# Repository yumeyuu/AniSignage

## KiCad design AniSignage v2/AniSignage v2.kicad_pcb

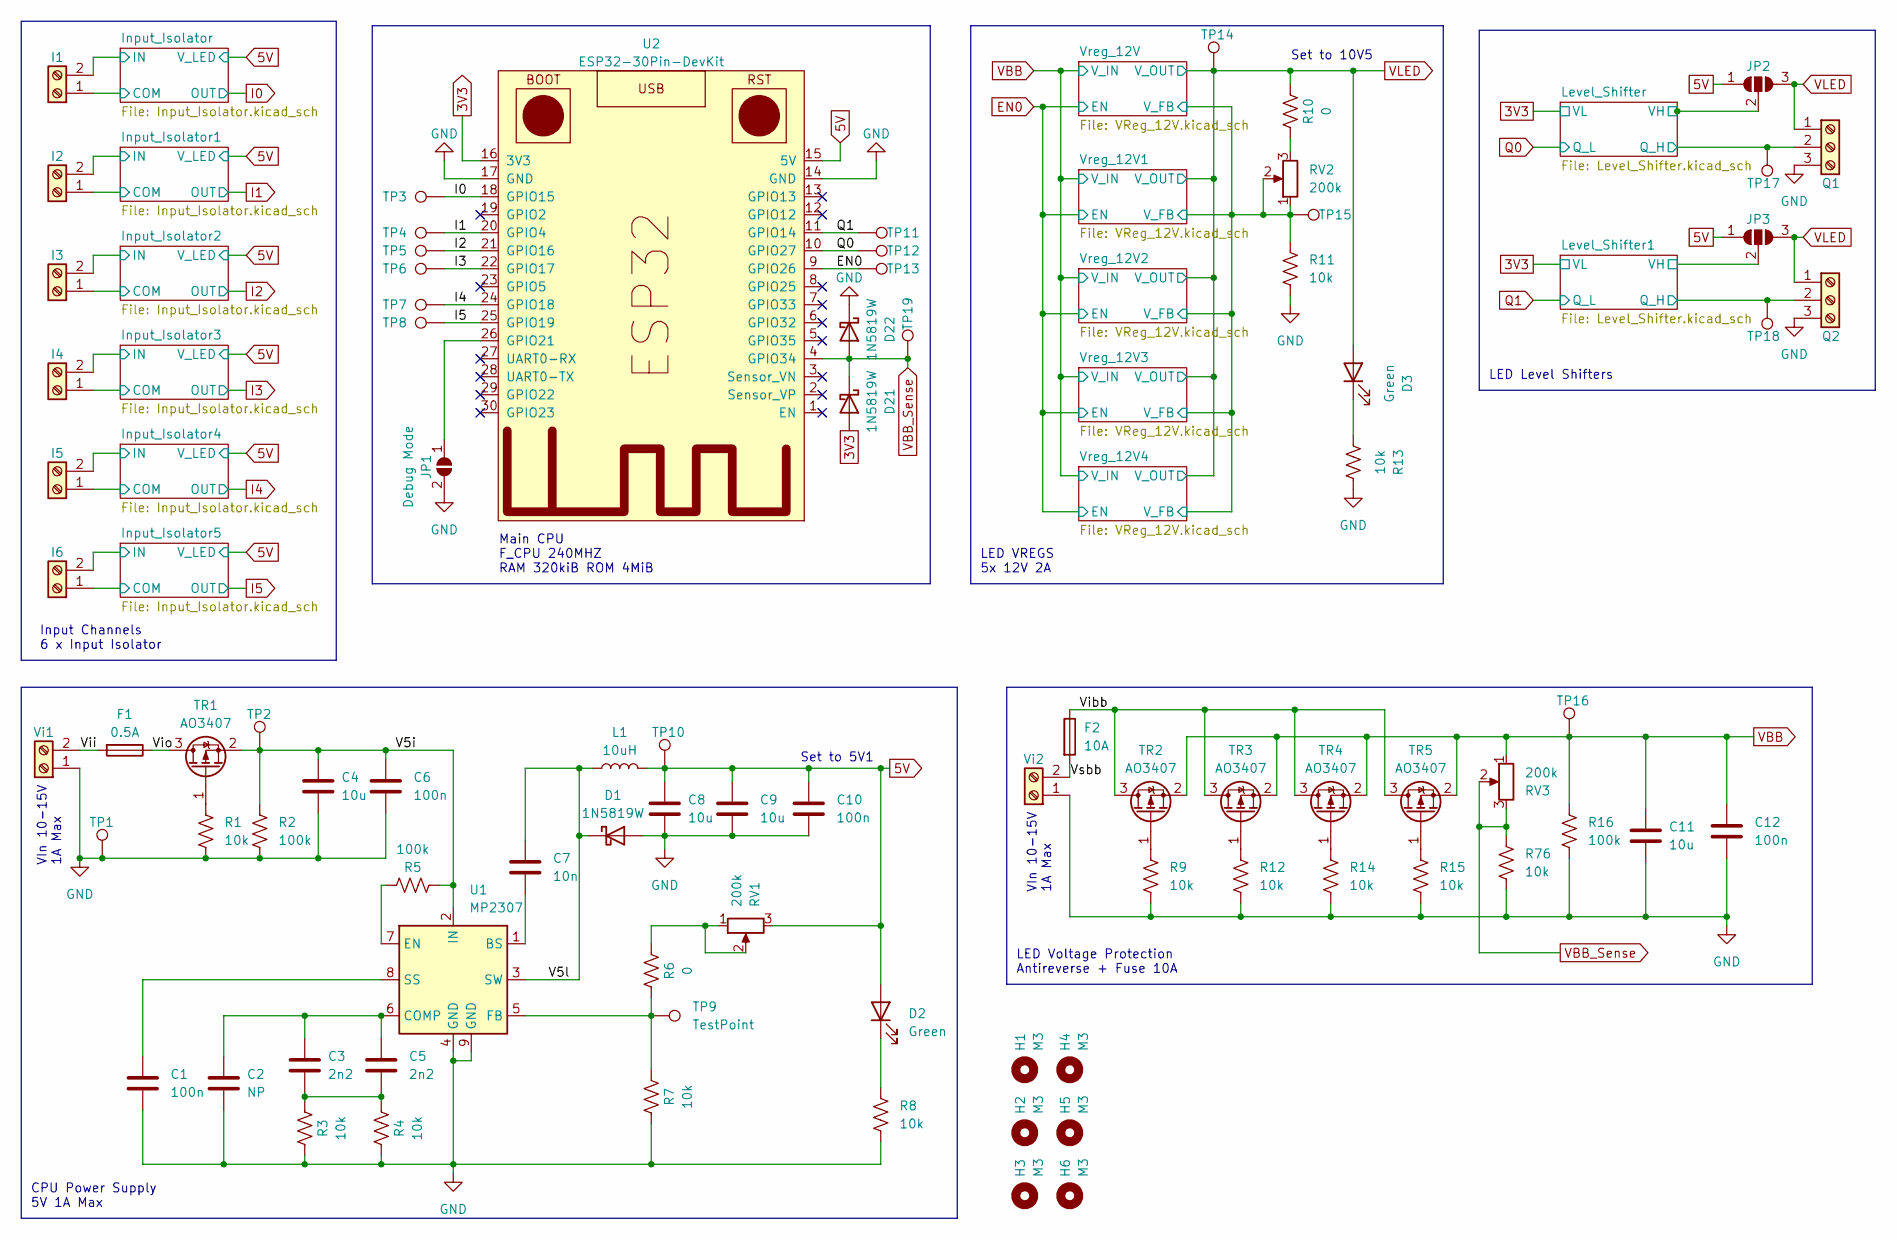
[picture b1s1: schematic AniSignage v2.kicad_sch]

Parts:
C1, C6, C10, C12: 100n; C_0603_1608Metric
C2: NP; C_0603_1608Metric
C3, C5: 2n2; C_0603_1608Metric
C4, C8, C9, C11: 10u; C_1206_3216Metric
C7: 10n; C_0603_1608Metric
D1, D21, D22: 1N5819W; D_SOD-123F
D2, D3: Green; LED_0805_2012Metric
F1: 0.5A; Fuse_1812_4532Metric
F2: 10A; Fuse_Bourns_MF-RG1100
H1, H2, H3, H4, H5, H6: M3; MountingHole_3.2mm_M3
I1, I2, I3, I4, I5, I6: Screw_Terminal_01x02; TerminalBlock_4Ucon_1x02_P3.50mm_Horizontal
JP1: Debug Mode; SolderJumper-2_P1.3mm_Open_TrianglePad1.0x1.5mm
JP2, JP3: SolderJumper_3_Open; SolderJumper-3_P2.0mm_Open_TrianglePad1.0x1.5mm
L1: 10uH; L_Neosid_SM-NE127_HandSoldering
Q1, Q2: Screw_Terminal_01x03; TerminalBlock_4Ucon_1x03_P3.50mm_Horizontal
R1, R3, R4, R7, R8, R9, R11, R12, R13, R14, R15, R76: 10k; R_0603_1608Metric
R2, R5, R16: 100k; R_0603_1608Metric
R6, R10: 0; R_0603_1608Metric
RV1, RV2, RV3: 200k; Potentiometer_Bourns_3269W_Vertical
TP1, TP2, TP3, TP4, TP5, TP6, TP7, TP8, TP9, TP10, TP11, TP12, TP13, TP14, TP15, TP16, TP17, TP18, TP19: TestPoint; TestPoint_Pad_D2.0mm
TR1, TR2, TR3, TR4, TR5: AO3407; SOT-23
U1: MP2307; SOIC-8-1EP_3.9x4.9mm_P1.27mm_EP2.62x3.51mm
U2: ESP32-30Pin-DevKit; ESP32-Devkit-30p-v2
Vi1, Vi2: Screw_Terminal_01x02; TerminalBlock_bornier-2_P5.08mm

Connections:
3V3: D21.2 (A), U2.16 (3V3); also elsewhere on the board
5V: C8.2, C9.1, C10.1, D2.2 (A), JP2.1 (A), JP3.1 (A), L1.2, RV1.3, TP10.1, U2.15 (5V); also elsewhere on the board
/Input_Isolator1/COM: I2.1; also elsewhere on the board
/Input_Isolator1/IN: I2.2; also elsewhere on the board
/Input_Isolator2/COM: I3.1; also elsewhere on the board
/Input_Isolator2/IN: I3.2; also elsewhere on the board
/Input_Isolator3/COM: I4.1; also elsewhere on the board
/Input_Isolator3/IN: I4.2; also elsewhere on the board
/Input_Isolator4/COM: I5.1; also elsewhere on the board
/Input_Isolator4/IN: I5.2; also elsewhere on the board
/Input_Isolator5/COM: I6.1; also elsewhere on the board
/Input_Isolator5/IN: I6.2; also elsewhere on the board
/Input_Isolator/COM: I1.1; also elsewhere on the board
/Input_Isolator/IN: I1.2; also elsewhere on the board
/Level_Shifter1/Q_H: Q2.2, TP18.1; also elsewhere on the board
/Level_Shifter1/VH: JP3.2 (C); also elsewhere on the board
/Level_Shifter/Q_H: Q1.2, TP17.1; also elsewhere on the board
/Level_Shifter/VH: JP2.2 (C); also elsewhere on the board
/V5i: C4.2, C6.1, R2.1, R5.1, TP2.1, TR1.2 (S), U1.2 (IN)
/V5l: C7.2, D1.1 (K), L1.1, U1.3 (SW)
/Vibb: F2.1, TR2.3 (D), TR3.3 (D), TR4.3 (D), TR5.3 (D)
/Vii: F1.2, Vi1.2
/Vio: F1.1, TR1.3 (D)
/Vreg_12V/V_FB: R11.1, RV2.1, RV2.2, TP15.1; also elsewhere on the board
/Vsbb: F2.2, Vi2.2
EN0: TP13.1, U2.9 (GPIO26); also elsewhere on the board
GND: C1.2, C2.2, C4.1, C6.2, C8.1, C9.2, C10.2, C11.1, C12.2, D1.2 (A), D22.1 (K), JP1.2 (B), Q1.3, Q2.3, R1.2, R2.2, R3.1, R4.1, R7.1, R8.2, R9.2, R11.2, R12.2, R13.1, R14.2, R15.2, R16.2, R76.2, TP1.1, U1.4 (GND), U1.9 (GND), U2.14 (GND), U2.17 (GND), Vi1.1, Vi2.1; also elsewhere on the board
I0: TP3.1, U2.18 (GPIO15); also elsewhere on the board
I1: TP4.1, U2.20 (GPIO4); also elsewhere on the board
I2: TP5.1, U2.21 (GPIO16); also elsewhere on the board
I3: TP6.1, U2.22 (GPIO17); also elsewhere on the board
I4: TP7.1, U2.24 (GPIO18); also elsewhere on the board
I5: TP8.1, U2.25 (GPIO19); also elsewhere on the board
unnamed: C3.2, C5.2, R3.2, R4.2
unnamed: D2.1 (K), R8.1
unnamed: D3.1 (K), R13.2
unnamed: JP1.1 (A), U2.26 (GPIO21)
unnamed: R6.2, RV1.1, RV1.2
unnamed: R10.1, RV2.3
unnamed: R1.1, TR1.1 (G)
unnamed: R9.1, TR2.1 (G)
unnamed: R12.1, TR3.1 (G)
unnamed: R14.1, TR4.1 (G)
unnamed: R15.1, TR5.1 (G)
unnamed: C7.1, U1.1 (BS)
unnamed: C2.1, C3.1, C5.1, U1.6 (COMP)
unnamed: R5.2, U1.7 (EN)
unnamed: R6.1, R7.2, TP9.1, U1.5 (FB)
unnamed: C1.1, U1.8 (SS)
Q0: TP12.1, U2.10 (GPIO27); also elsewhere on the board
Q1: TP11.1, U2.11 (GPIO14); also elsewhere on the board
VBB: C11.2, C12.1, R16.1, RV3.1, TP16.1, TR2.2 (S), TR3.2 (S), TR4.2 (S), TR5.2 (S); also elsewhere on the board
VBB_Sense: D21.1 (K), D22.2 (A), R76.1, RV3.2, RV3.3, TP19.1, U2.4 (GPIO34)
VLED: D3.2 (A), JP2.3 (B), JP3.3 (B), Q1.1, Q2.1, R10.2, TP14.1; also elsewhere on the board

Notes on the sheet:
LED VREGS 5x 12V 2A
LED Voltage Protection Antireverse + Fuse 10A
VIn 10-15V 1A Max
Main CPU F_CPU 240MHZ RAM 320kiB ROM 4MiB
Set to 10V5
LED Level Shifters
CPU Power Supply 5V 1A Max
Input Channels 6 x Input Isolator
Set to 5V1

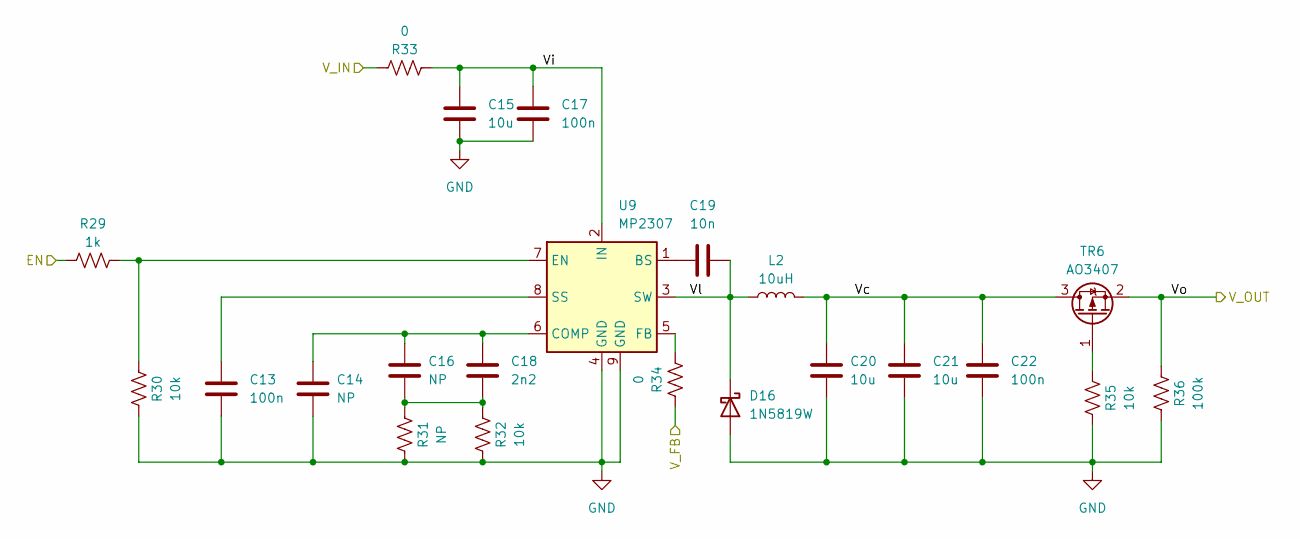
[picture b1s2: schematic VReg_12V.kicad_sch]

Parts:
C13, C17, C22: 100n; C_0603_1608Metric
C14, C16: NP; C_0603_1608Metric
C15, C20, C21: 10u; C_1206_3216Metric
C18: 2n2; C_0603_1608Metric
C19: 10n; C_0603_1608Metric
D16: 1N5819W; D_SOD-123F
L2: 10uH; L_Neosid_SM-NE127_HandSoldering
R29: 1k; R_0603_1608Metric
R30, R32, R35: 10k; R_0603_1608Metric
R31: NP; R_0603_1608Metric
R33, R34: 0; R_0603_1608Metric
R36: 100k; R_0603_1608Metric
TR6: AO3407; SOT-23
U9: MP2307; SOIC-8-1EP_3.9x4.9mm_P1.27mm_EP2.62x3.51mm

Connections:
/Vreg_12V/V_FB: R34.2; also elsewhere on the board
/Vreg_12V/Vc: C20.1, C21.1, C22.1, L2.2, TR6.3 (D)
/Vreg_12V/Vi: C15.1, C17.1, R33.1, U9.2 (IN)
/Vreg_12V/Vl: C19.2, D16.1 (K), L2.1, U9.3 (SW)
EN0: R29.2; also elsewhere on the board
GND: C13.2, C14.2, C15.2, C17.2, C20.2, C21.2, C22.2, D16.2 (A), R30.1, R31.1, R32.1, R35.1, R36.1, U9.4 (GND), U9.9 (GND); also elsewhere on the board
unnamed: C16.2, C18.2, R31.2, R32.2
unnamed: R35.2, TR6.1 (G)
unnamed: C19.1, U9.1 (BS)
unnamed: C14.1, C16.1, C18.1, U9.6 (COMP)
unnamed: R29.1, R30.2, U9.7 (EN)
unnamed: R34.1, U9.5 (FB)
unnamed: C13.1, U9.8 (SS)
VBB: R33.2; also elsewhere on the board
VLED: R36.2, TR6.2 (S); also elsewhere on the board

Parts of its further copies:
C23, C27, C32, C33, C37, C42, C43, C47, C52, C53, C57, C62: 100n; C_0603_1608Metric
C24, C26, C34, C36, C44, C46, C54, C56: NP; C_0603_1608Metric
C25, C30, C31, C35, C40, C41, C45, C50, C51, C55, C60, C61: 10u; C_1206_3216Metric
C28, C38, C48, C58: 2n2; C_0603_1608Metric
C29, C39, C49, C59: 10n; C_0603_1608Metric
D17, D18, D19, D20: 1N5819W; D_SOD-123F
L3, L4, L5, L6: 10uH; L_Neosid_SM-NE127_HandSoldering
R37, R45, R53, R61: 1k; R_0603_1608Metric
R38, R40, R43, R46, R48, R51, R54, R56, R59, R62, R64, R67: 10k; R_0603_1608Metric
R39, R47, R55, R63: NP; R_0603_1608Metric
R41, R42, R49, R50, R57, R58, R65, R66: 0; R_0603_1608Metric
R44, R52, R60, R68: 100k; R_0603_1608Metric
TR7, TR8, TR9, TR10: AO3407; SOT-23
U10, U11, U12, U13: MP2307; SOIC-8-1EP_3.9x4.9mm_P1.27mm_EP2.62x3.51mm

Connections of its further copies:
/Vreg_12V1/Vc: C30.1, C31.1, C32.1, L3.2, TR7.3 (D)
/Vreg_12V1/Vi: C25.1, C27.1, R41.1, U10.2 (IN)
/Vreg_12V1/Vl: C29.2, D17.1 (K), L3.1, U10.3 (SW)
/Vreg_12V2/Vc: C40.1, C41.1, C42.1, L4.2, TR8.3 (D)
/Vreg_12V2/Vi: C35.1, C37.1, R49.1, U11.2 (IN)
/Vreg_12V2/Vl: C39.2, D18.1 (K), L4.1, U11.3 (SW)
/Vreg_12V3/Vc: C50.1, C51.1, C52.1, L5.2, TR9.3 (D)
/Vreg_12V3/Vi: C45.1, C47.1, R57.1, U12.2 (IN)
/Vreg_12V3/Vl: C49.2, D19.1 (K), L5.1, U12.3 (SW)
/Vreg_12V4/Vc: C60.1, C61.1, C62.1, L6.2, TR10.3 (D)
/Vreg_12V4/Vi: C55.1, C57.1, R65.1, U13.2 (IN)
/Vreg_12V4/Vl: C59.2, D20.1 (K), L6.1, U13.3 (SW)
/Vreg_12V/V_FB: R42.2, R50.2, R58.2, R66.2; also elsewhere on the board
EN0: R37.2, R45.2, R53.2, R61.2; also elsewhere on the board
GND: C23.2, C24.2, C25.2, C27.2, C30.2, C31.2, C32.2, C33.2, C34.2, C35.2, C37.2, C40.2, C41.2, C42.2, C43.2, C44.2, C45.2, C47.2, C50.2, C51.2, C52.2, C53.2, C54.2, C55.2, C57.2, C60.2, C61.2, C62.2, D17.2 (A), D18.2 (A), D19.2 (A), D20.2 (A), R38.1, R39.1, R40.1, R43.1, R44.1, R46.1, R47.1, R48.1, R51.1, R52.1, R54.1, R55.1, R56.1, R59.1, R60.1, R62.1, R63.1, R64.1, R67.1, R68.1, U10.4 (GND), U10.9 (GND), U11.4 (GND), U11.9 (GND), U12.4 (GND), U12.9 (GND), U13.4 (GND), U13.9 (GND); also elsewhere on the board
unnamed: C26.2, C28.2, R39.2, R40.2
unnamed: C36.2, C38.2, R47.2, R48.2
unnamed: C46.2, C48.2, R55.2, R56.2
unnamed: C56.2, C58.2, R63.2, R64.2
unnamed: R43.2, TR7.1 (G)
unnamed: R51.2, TR8.1 (G)
unnamed: R59.2, TR9.1 (G)
unnamed: R67.2, TR10.1 (G)
unnamed: C29.1, U10.1 (BS)
unnamed: C24.1, C26.1, C28.1, U10.6 (COMP)
unnamed: R37.1, R38.2, U10.7 (EN)
unnamed: R42.1, U10.5 (FB)
unnamed: C23.1, U10.8 (SS)
unnamed: C39.1, U11.1 (BS)
unnamed: C34.1, C36.1, C38.1, U11.6 (COMP)
unnamed: R45.1, R46.2, U11.7 (EN)
unnamed: R50.1, U11.5 (FB)
unnamed: C33.1, U11.8 (SS)
unnamed: C49.1, U12.1 (BS)
unnamed: C44.1, C46.1, C48.1, U12.6 (COMP)
unnamed: R53.1, R54.2, U12.7 (EN)
unnamed: R58.1, U12.5 (FB)
unnamed: C43.1, U12.8 (SS)
unnamed: C59.1, U13.1 (BS)
unnamed: C54.1, C56.1, C58.1, U13.6 (COMP)
unnamed: R61.1, R62.2, U13.7 (EN)
unnamed: R66.1, U13.5 (FB)
unnamed: C53.1, U13.8 (SS)
VBB: R41.2, R49.2, R57.2, R65.2; also elsewhere on the board
VLED: R44.2, R52.2, R60.2, R68.2, TR7.2 (S), TR8.2 (S), TR9.2 (S), TR10.2 (S); also elsewhere on the board

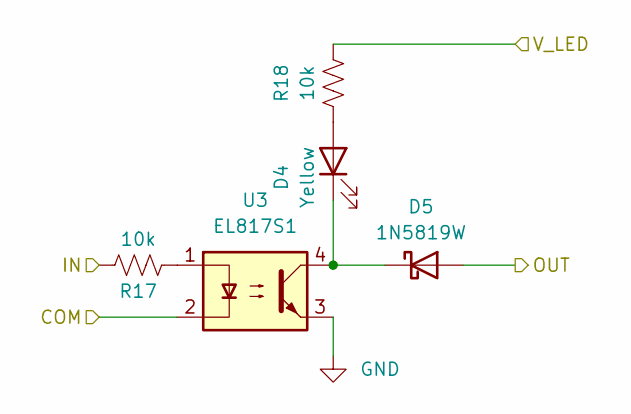
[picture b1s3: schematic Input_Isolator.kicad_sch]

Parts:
D4: Yellow; LED_0805_2012Metric
D5: 1N5819W; D_SOD-123F
R17, R18: 10k; R_0603_1608Metric
U3: EL817S1; DIP-4_W7.62mm_SMDSocket_SmallPads

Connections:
5V: R18.2; also elsewhere on the board
/Input_Isolator/COM: U3.2; also elsewhere on the board
/Input_Isolator/IN: R17.1; also elsewhere on the board
GND: U3.3; also elsewhere on the board
I0: D5.2 (A); also elsewhere on the board
unnamed: D4.2 (A), R18.1
unnamed: D4.1 (K), D5.1 (K), U3.4
unnamed: R17.2, U3.1

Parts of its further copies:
D6, D8, D10, D12, D14: Yellow; LED_0805_2012Metric
D7, D9, D11, D13, D15: 1N5819W; D_SOD-123F
R19, R20, R21, R22, R23, R24, R25, R26, R27, R28: 10k; R_0603_1608Metric
U4, U5, U6, U7, U8: EL817S1; DIP-4_W7.62mm_SMDSocket_SmallPads

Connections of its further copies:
5V: R20.2, R22.2, R24.2, R26.2, R28.2; also elsewhere on the board
/Input_Isolator1/COM: U4.2; also elsewhere on the board
/Input_Isolator1/IN: R19.1; also elsewhere on the board
/Input_Isolator2/COM: U5.2; also elsewhere on the board
/Input_Isolator2/IN: R21.1; also elsewhere on the board
/Input_Isolator3/COM: U6.2; also elsewhere on the board
/Input_Isolator3/IN: R23.1; also elsewhere on the board
/Input_Isolator4/COM: U7.2; also elsewhere on the board
/Input_Isolator4/IN: R25.1; also elsewhere on the board
/Input_Isolator5/COM: U8.2; also elsewhere on the board
/Input_Isolator5/IN: R27.1; also elsewhere on the board
GND: U4.3, U5.3, U6.3, U7.3, U8.3; also elsewhere on the board
I1: D7.2 (A); also elsewhere on the board
I2: D9.2 (A); also elsewhere on the board
I3: D11.2 (A); also elsewhere on the board
I4: D13.2 (A); also elsewhere on the board
I5: D15.2 (A); also elsewhere on the board
unnamed: D6.2 (A), R20.1
unnamed: D6.1 (K), D7.1 (K), U4.4
unnamed: D8.2 (A), R22.1
unnamed: D8.1 (K), D9.1 (K), U5.4
unnamed: D10.2 (A), R24.1
unnamed: D10.1 (K), D11.1 (K), U6.4
unnamed: D12.2 (A), R26.1
unnamed: D12.1 (K), D13.1 (K), U7.4
unnamed: D14.2 (A), R28.1
unnamed: D14.1 (K), D15.1 (K), U8.4
unnamed: R19.2, U4.1
unnamed: R21.2, U5.1
unnamed: R23.2, U6.1
unnamed: R25.2, U7.1
unnamed: R27.2, U8.1

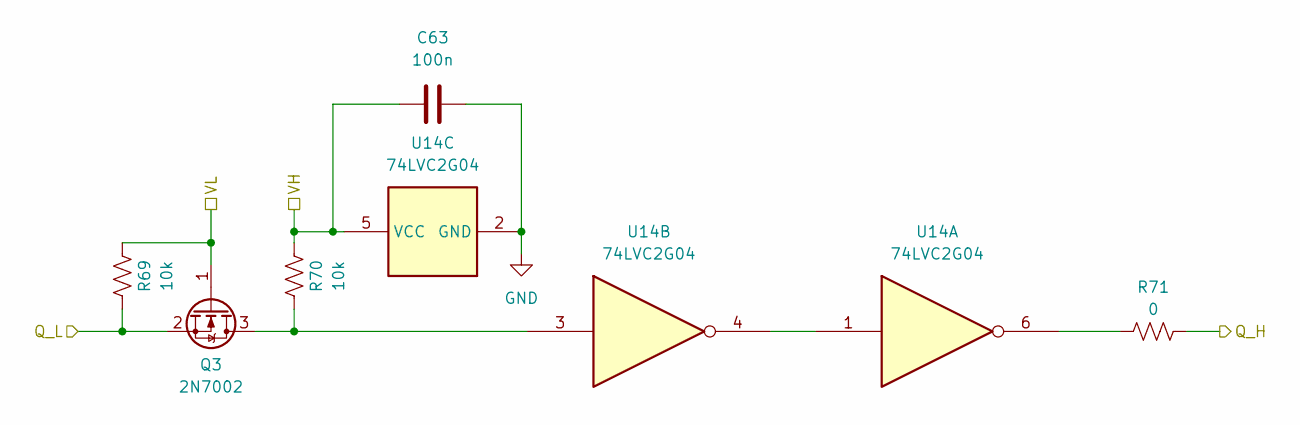
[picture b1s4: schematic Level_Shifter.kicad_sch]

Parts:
C63: 100n; C_0603_1608Metric
Q3: 2N7002; SOT-23
R69, R70: 10k; R_0603_1608Metric
R71: 0; R_0603_1608Metric
U14: 74LVC2G04; SOT-363_SC-70-6

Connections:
3V3: Q3.1 (G), R69.2; also elsewhere on the board
/Level_Shifter/Q_H: R71.2; also elsewhere on the board
/Level_Shifter/VH: C63.1, R70.2, U14.5 (VCC); also elsewhere on the board
GND: C63.2, U14.2 (GND); also elsewhere on the board
unnamed: Q3.3 (D), R70.1, U14.3
unnamed: R71.1, U14.6
unnamed: U14.1, U14.4
Q0: Q3.2 (S), R69.1; also elsewhere on the board

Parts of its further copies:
C64: 100n; C_0603_1608Metric
Q4: 2N7002; SOT-23
R72, R73: 10k; R_0603_1608Metric
R74: 0; R_0603_1608Metric
U15: 74LVC2G04; SOT-363_SC-70-6

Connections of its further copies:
3V3: Q4.1 (G), R72.2; also elsewhere on the board
/Level_Shifter1/Q_H: R74.2; also elsewhere on the board
/Level_Shifter1/VH: C64.1, R73.2, U15.5 (VCC); also elsewhere on the board
GND: C64.2, U15.2 (GND); also elsewhere on the board
unnamed: Q4.3 (D), R73.1, U15.3
unnamed: R74.1, U15.6
unnamed: U15.1, U15.4
Q1: Q4.2 (S), R72.1; also elsewhere on the board

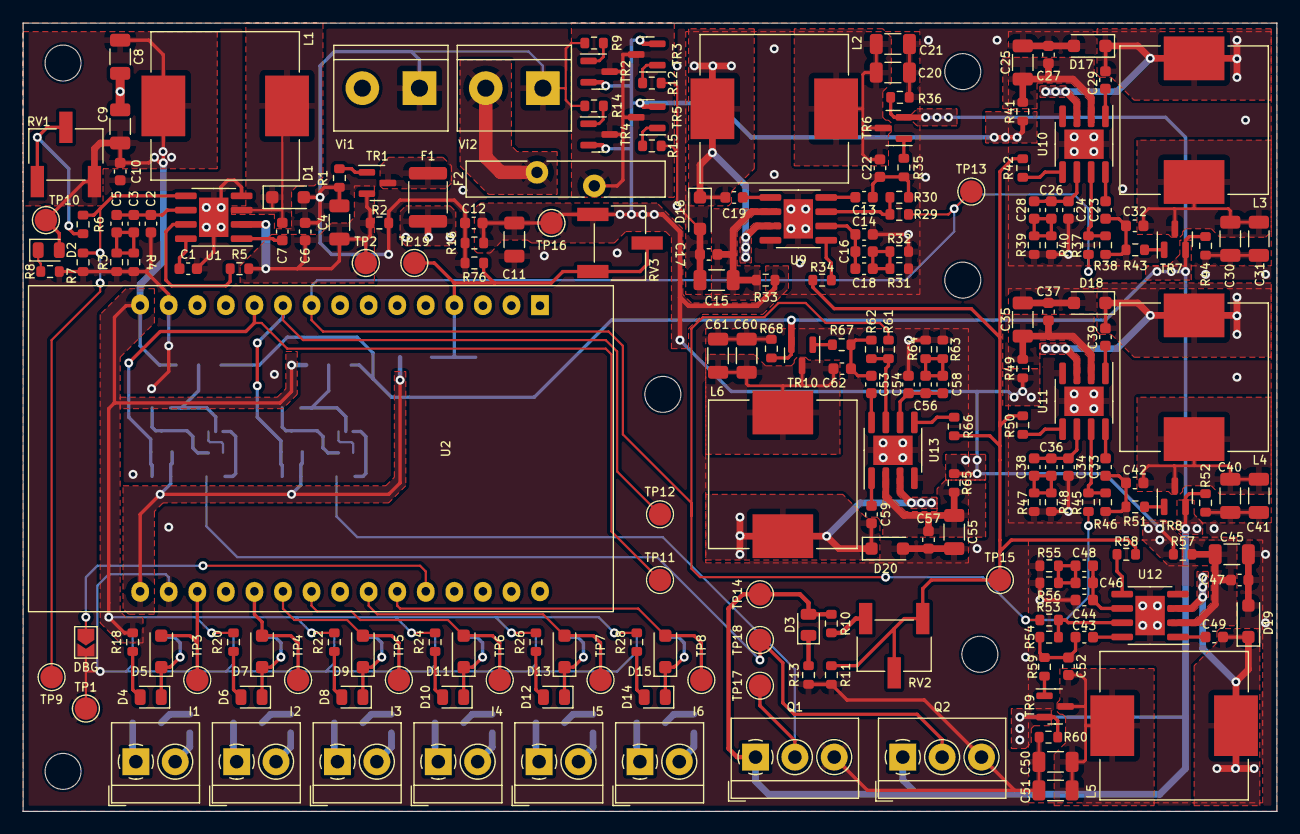
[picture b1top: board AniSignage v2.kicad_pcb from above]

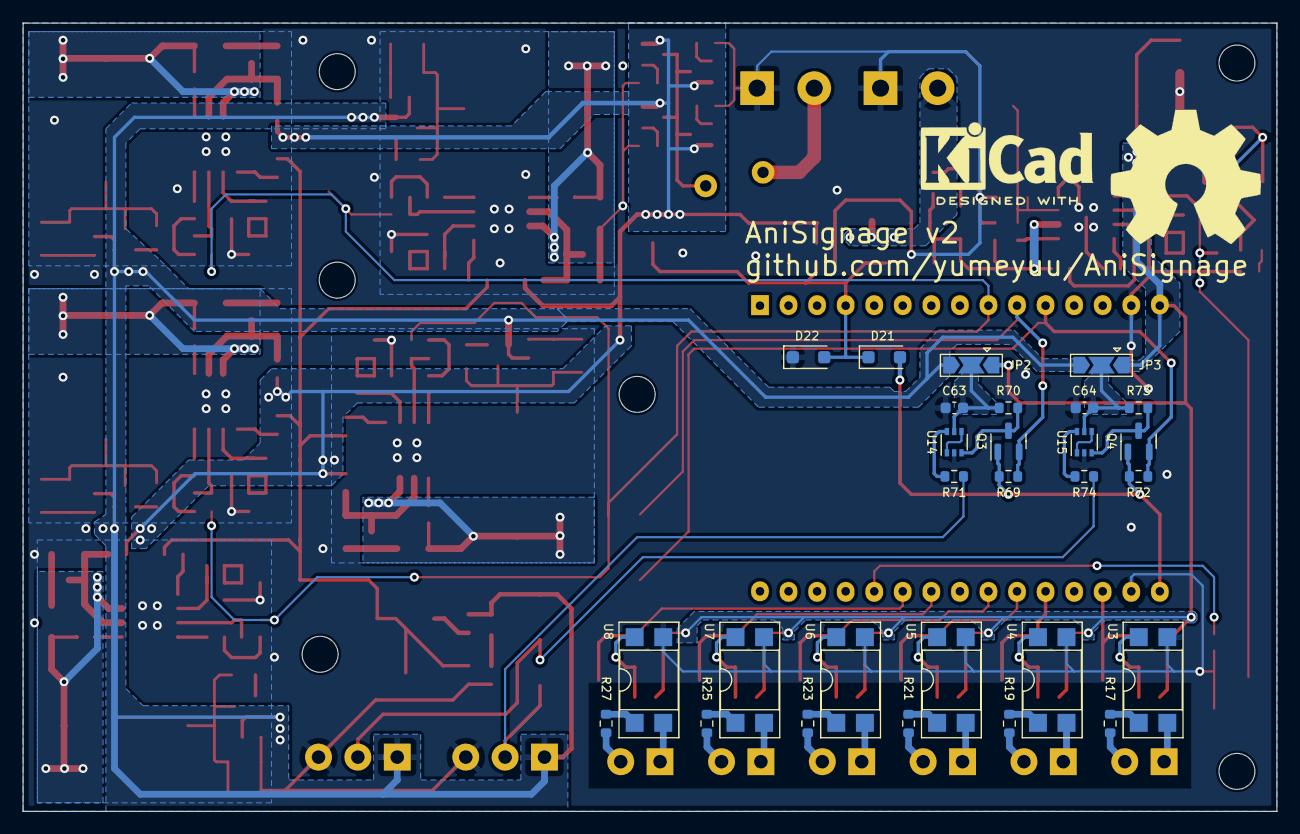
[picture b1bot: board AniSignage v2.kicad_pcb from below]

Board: 2 copper layers, 111.5 x 70.1 mm, 237 parts (28 on the bottom side), 128 nets.

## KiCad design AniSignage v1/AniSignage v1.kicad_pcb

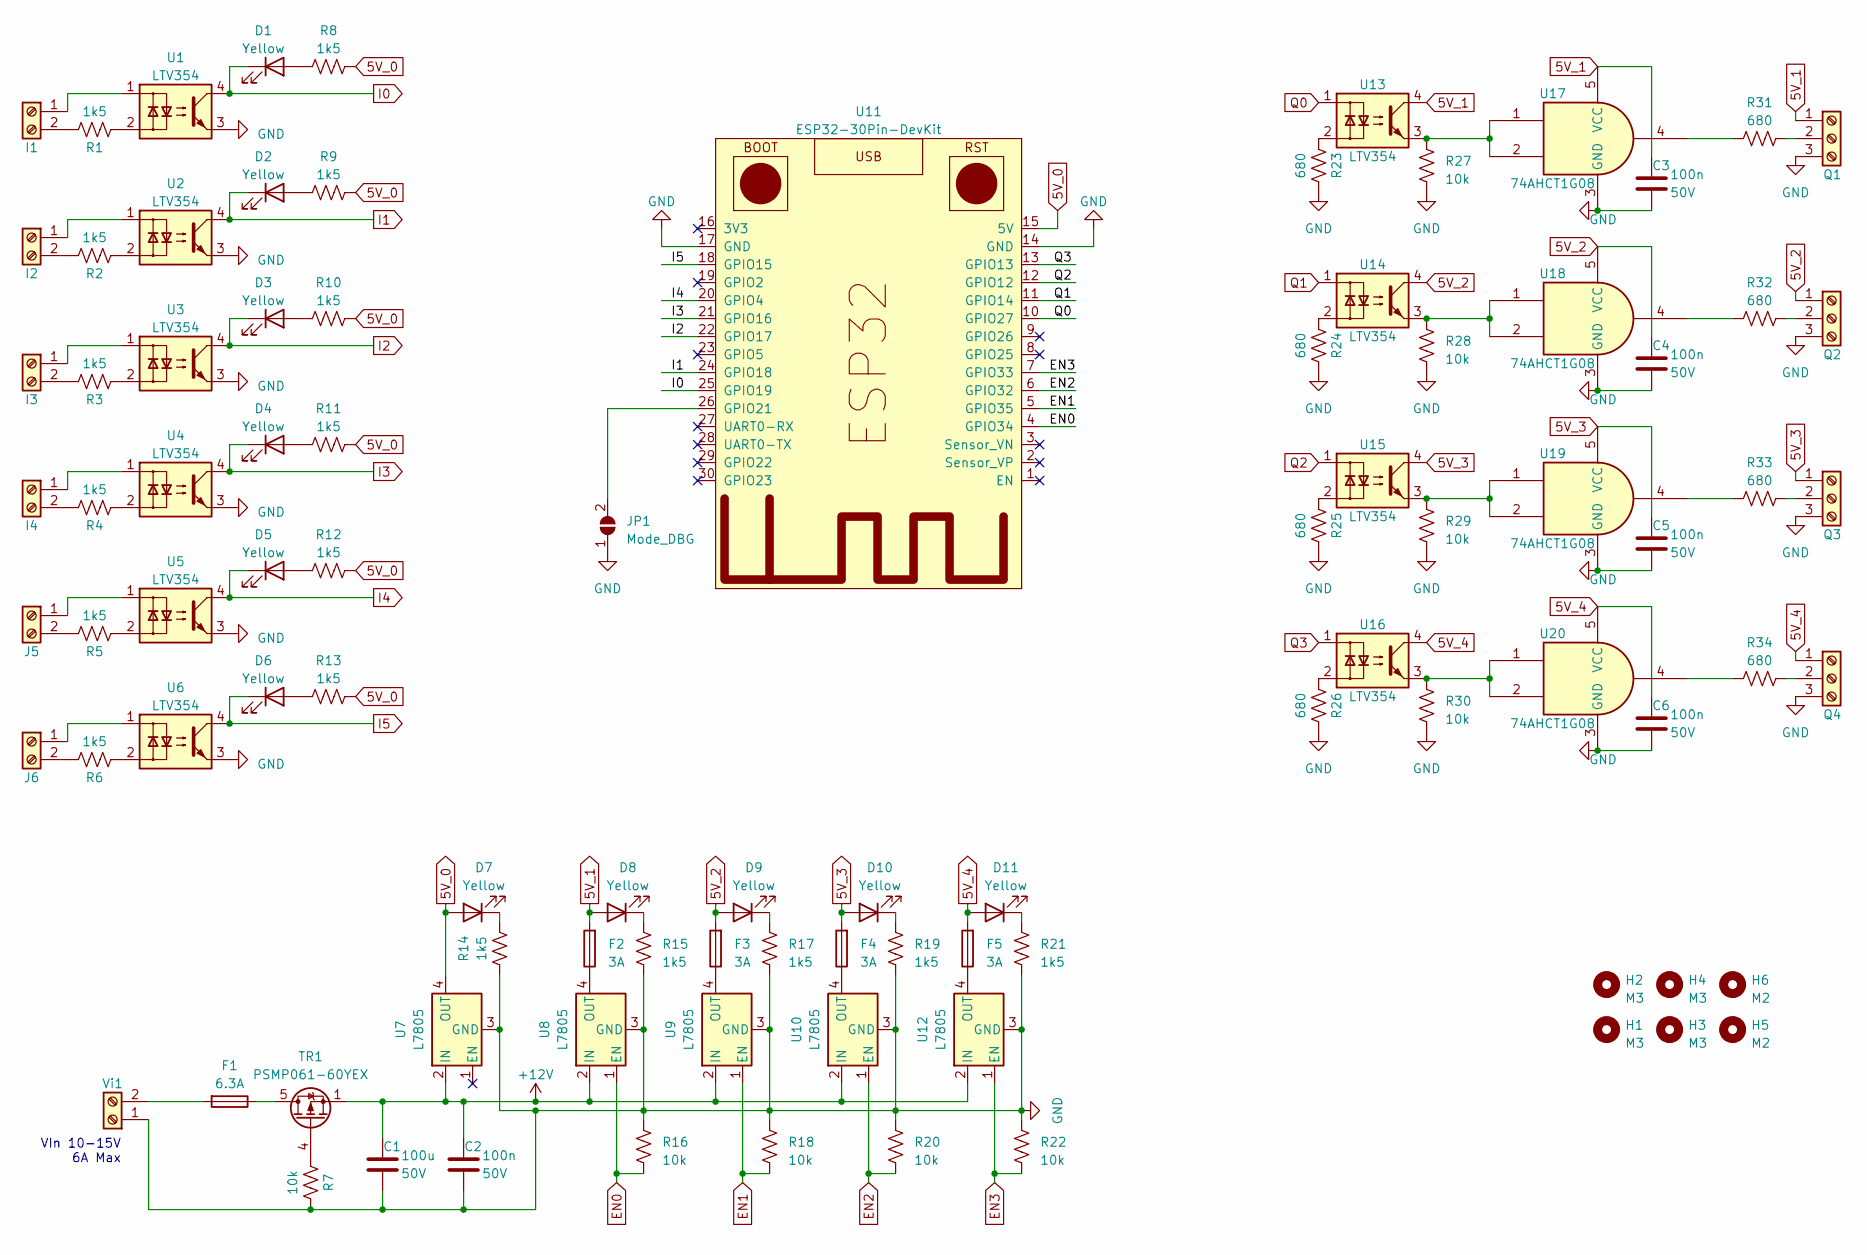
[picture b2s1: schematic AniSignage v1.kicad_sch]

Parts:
C1: 100u; C_1206_3216Metric; Voltage 50V
C2, C3, C4, C5, C6: 100n; C_0805_2012Metric; Voltage 50V
D1, D2, D3, D4, D5, D6, D7, D8, D9, D10, D11: Yellow; LED_0603_1608Metric
F1: 6.3A; Fuseholder_Littelfuse_Nano2_154x
F2, F3, F4, F5: 3A; Fuseholder_Littelfuse_Nano2_154x
H1, H2, H3, H4: M3; MountingHole_3.2mm_M3
H5, H6: M2; MountingHole_2.2mm_M2
I1, I2, I3, I4: Screw_Terminal_01x02; TerminalBlock_Phoenix_MPT-0,5-2-2.54_1x02_P2.54mm_Horizontal
J5, J6: Screw_Terminal_01x02; TerminalBlock_Phoenix_MPT-0,5-2-2.54_1x02_P2.54mm_Horizontal
JP1: Mode_DBG; SolderJumper-2_P1.3mm_Open_TrianglePad1.0x1.5mm
Q1, Q2, Q3, Q4: Screw_Terminal_01x03; TerminalBlock_Phoenix_MPT-0,5-3-2.54_1x03_P2.54mm_Horizontal
R1, R2, R3, R4, R5, R6, R8, R9, R10, R11, R12, R13, R14, R15, R17, R19, R21: 1k5; R_0603_1608Metric
R7, R16, R18, R20, R22, R27, R28, R29, R30: 10k; R_0603_1608Metric
R23, R24, R25, R26, R31, R32, R33, R34: 680; R_0603_1608Metric
TR1: PSMP061-60YEX; LFPAK56
U1, U2, U3, U4, U5, U6, U13, U14, U15, U16: LTV354; DIP-4_W7.62mm_SMDSocket_SmallPads
U7, U8, U9, U10, U12: L7805; Vreg_Module
U11: ESP32-30Pin-DevKit; ESP32-Devkit-30p
U17, U18, U19, U20: 74AHCT1G08; SOT-353_SC-70-5
Vi1: Screw_Terminal_01x02; TerminalBlock_Phoenix_MKDS-1,5-2-5.08_1x02_P5.08mm_Horizont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

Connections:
5V_0: D7.2 (A), R8.2, R9.2, R10.2, R11.2, R12.2, R13.2, U7.4 (OUT), U11.15 (5V)
5V_1: C3.1, D8.2 (A), F2.2, Q1.1, U13.4, U17.5 (VCC)
5V_2: C4.1, D9.2 (A), F3.2, Q2.1, U14.4, U18.5 (VCC)
5V_3: C5.1, D10.2 (A), F4.2, Q3.1, U15.4, U19.5 (VCC)
5V_4: C6.1, D11.2 (A), F5.2, Q4.1, U16.4, U20.5 (VCC)
+12V: C1.1, C2.1, TR1.1 (S), TR1.2 (S), TR1.3 (S), U7.2 (IN), U8.2 (IN), U9.2 (IN), U10.2 (IN), U12.2 (IN)
EN0: R16.1, U8.1 (EN), U11.4 (GPIO34)
EN1: R18.1, U9.1 (EN), U11.5 (GPIO35)
EN2: R20.1, U10.1 (EN), U11.6 (GPIO32)
EN3: R22.1, U11.7 (GPIO33), U12.1 (EN)
GND: C1.2, C2.2, C3.2, C4.2, C5.2, C6.2, JP1.1 (A), Q1.3, Q2.3, Q3.3, Q4.3, R7.1, R14.1, R15.1, R16.2, R17.1, R18.2, R19.1, R20.2, R21.1, R22.2, R23.1, R24.1, R25.1, R26.1, R27.2, R28.2, R29.2, R30.2, U1.3, U2.3, U3.3, U4.3, U5.3, U6.3, U7.3 (GND), U8.3 (GND), U9.3 (GND), U10.3 (GND), U11.14 (GND), U11.17 (GND), U12.3 (GND), U17.3 (GND), U18.3 (GND), U19.3 (GND), U20.3 (GND), Vi1.1
I0: D1.1 (K), U1.4, U11.25 (GPIO19)
I1: D2.1 (K), U2.4, U11.24 (GPIO18)
I2: D3.1 (K), U3.4, U11.22 (GPIO17)
I3: D4.1 (K), U4.4, U11.21 (GPIO16)
I4: D5.1 (K), U5.4, U11.20 (GPIO4)
I5: D6.1 (K), U6.4, U11.18 (GPIO15)
unnamed: D1.2 (A), R8.1
unnamed: D2.2 (A), R9.1
unnamed: D3.2 (A), R10.1
unnamed: D4.2 (A), R11.1
unnamed: D5.2 (A), R12.1
unnamed: D6.2 (A), R13.1
unnamed: D7.1 (K), R14.2
unnamed: D8.1 (K), R15.2
unnamed: D9.1 (K), R17.2
unnamed: D10.1 (K), R19.2
unnamed: D11.1 (K), R21.2
unnamed: I1.1, U1.1
unnamed: I1.2, R1.1
unnamed: I2.1, U2.1
unnamed: I2.2, R2.1
unnamed: I3.1, U3.1
unnamed: I3.2, R3.1
unnamed: I4.1, U4.1
unnamed: I4.2, R4.1
unnamed: J5.1, U5.1
unnamed: J5.2, R5.1
unnamed: J6.1, U6.1
unnamed: J6.2, R6.1
unnamed: JP1.2 (B), U11.26 (GPIO21)
unnamed: Q1.2, R31.2
unnamed: Q2.2, R32.2
unnamed: Q3.2, R33.2
unnamed: Q4.2, R34.2
unnamed: R1.2, U1.2
unnamed: R2.2, U2.2
unnamed: R3.2, U3.2
unnamed: R4.2, U4.2
unnamed: R5.2, U5.2
unnamed: R6.2, U6.2
unnamed: R23.2, U13.2
unnamed: R24.2, U14.2
unnamed: R25.2, U15.2
unnamed: R26.2, U16.2
unnamed: R27.1, U13.3, U17.1, U17.2
unnamed: R28.1, U14.3, U18.1, U18.2
unnamed: R29.1, U15.3, U19.1, U19.2
unnamed: R30.1, U16.3, U20.1, U20.2
unnamed: R31.1, U17.4
unnamed: R32.1, U18.4
unnamed: R33.1, U19.4
unnamed: R34.1, U20.4
unnamed: F1.1, TR1.5 (D)
unnamed: R7.2, TR1.4 (G)
unnamed: F2.1, U8.4 (OUT)
unnamed: F3.1, U9.4 (OUT)
unnamed: F4.1, U10.4 (OUT)
unnamed: F5.1, U12.4 (OUT)
unnamed: F1.2, Vi1.2
Q0: U11.10 (GPIO27), U13.1
Q1: U11.11 (GPIO14), U14.1
Q2: U11.12 (GPIO12), U15.1
Q3: U11.13 (GPIO13), U16.1

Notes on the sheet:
VIn 10-15V 6A Max

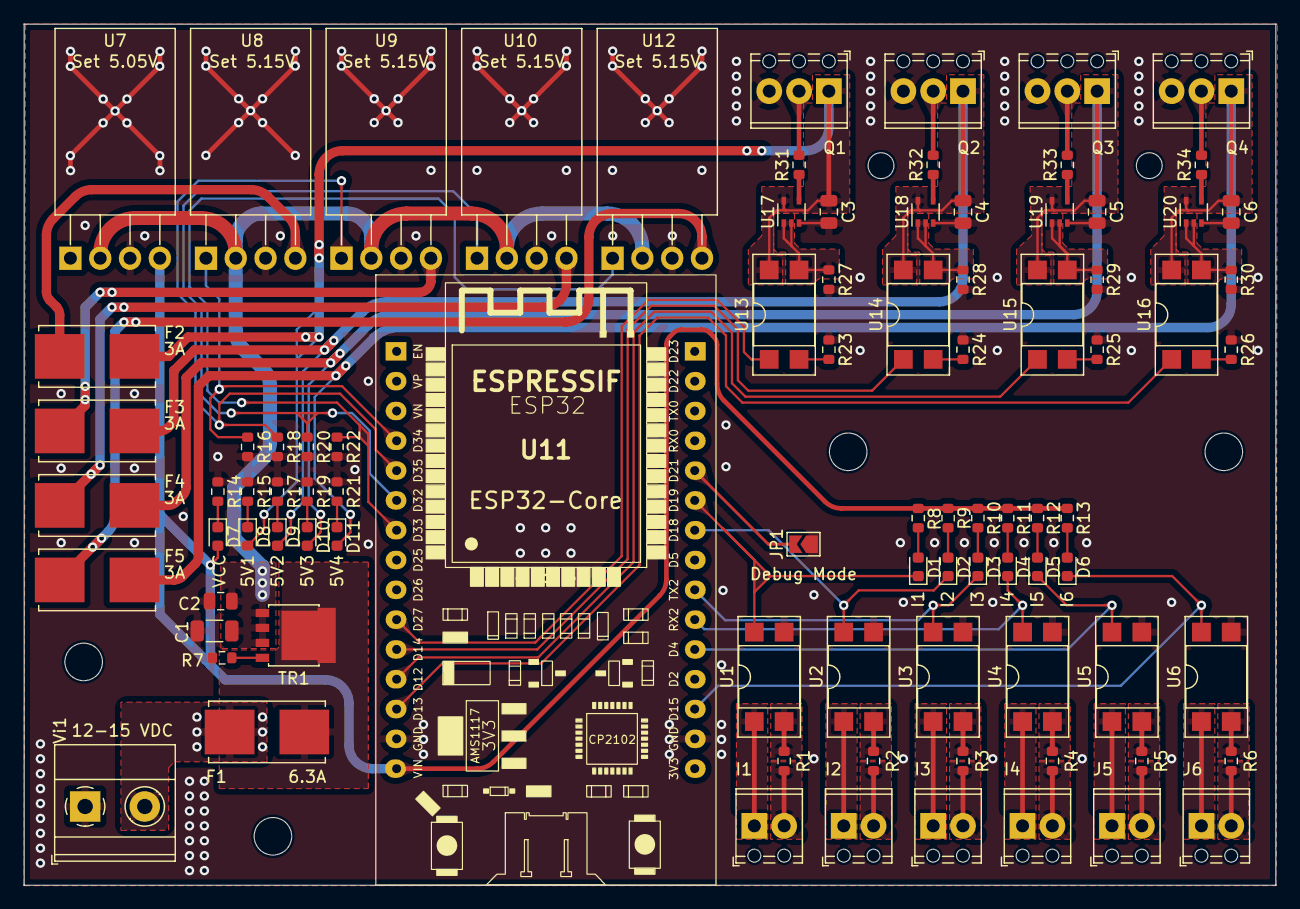
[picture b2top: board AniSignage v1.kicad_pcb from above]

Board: 2 copper layers, 106.7 x 73.4 mm, 95 parts (0 on the bottom side), 74 nets.

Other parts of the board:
H7: M2; MountingHole_2.2mm_M2

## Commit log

2024-02-13 Uploaded v1
    Uploading v1 of the PCB design
2024-03-14 Sync hardware design
    add revision 2 hardware design.
